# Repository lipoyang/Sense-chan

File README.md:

# ｾﾝｽﾁｬﾝ (Sense-chan)
ｾﾝｽﾁｬﾝはｽﾀｯｸﾁｬﾝ派生のSPRESENSEマイコン搭載ロボットです。  
SPRESENSE搭載のロボット用基板と対向2輪型ロボットおよびそのソフトウェアで構成されます。

## 解説

* [センスチャン ～ ｽﾀｯｸﾁｬﾝ派生のSPRESENSE搭載ロボット ～ by lipoyang | elchika](https://elchika.com/article/c5d4bbd1-0e7f-4fa6-907b-d6d020c664f9)

## ファイル
* [firmware](./firmware/) : ファームウェアのソースコード
* [mechanical](./mechanical/) : メカ部品のSTEPファイルとSTLファイル
* [board](./board/) : プリント基板の回路図とパターン設計

## SDカードにコピーするファイル

下記のファイルをマイクロSDカードにコピーして、ｾﾝｽﾁｬﾝのマイクロSDカードスロットに挿入してください。
* [fs_efont_ja_16.bin](./firmware/Sense-chan/sd_data/fs_efont_ja_16.bin) : フォントデータ
* [config.json](./firmware/Sense-chan/sd_data/config.json) : 設定ファイル

## 原典
このプロジェクトはｽﾀｯｸﾁｬﾝにインスパイアされた派生作品です。[ｽﾀｯｸﾁｬﾝ](https://github.com/stack-chan/stack-chan)は[ししかわ](https://x.com/stack_chan)さんが開発、公開している、 手乗りサイズのｽｰﾊﾟｰｶﾜｲｲコミュニケーションロボットです。

また、[B-SKY-Lab](https://x.com/eternalfriend17)さんが開発、公開している[ﾀｲﾘﾝﾁｬﾝ](https://github.com/kim-xps12/bsl-balancer)の機構設計やソフトウェアを一部参考にしています。

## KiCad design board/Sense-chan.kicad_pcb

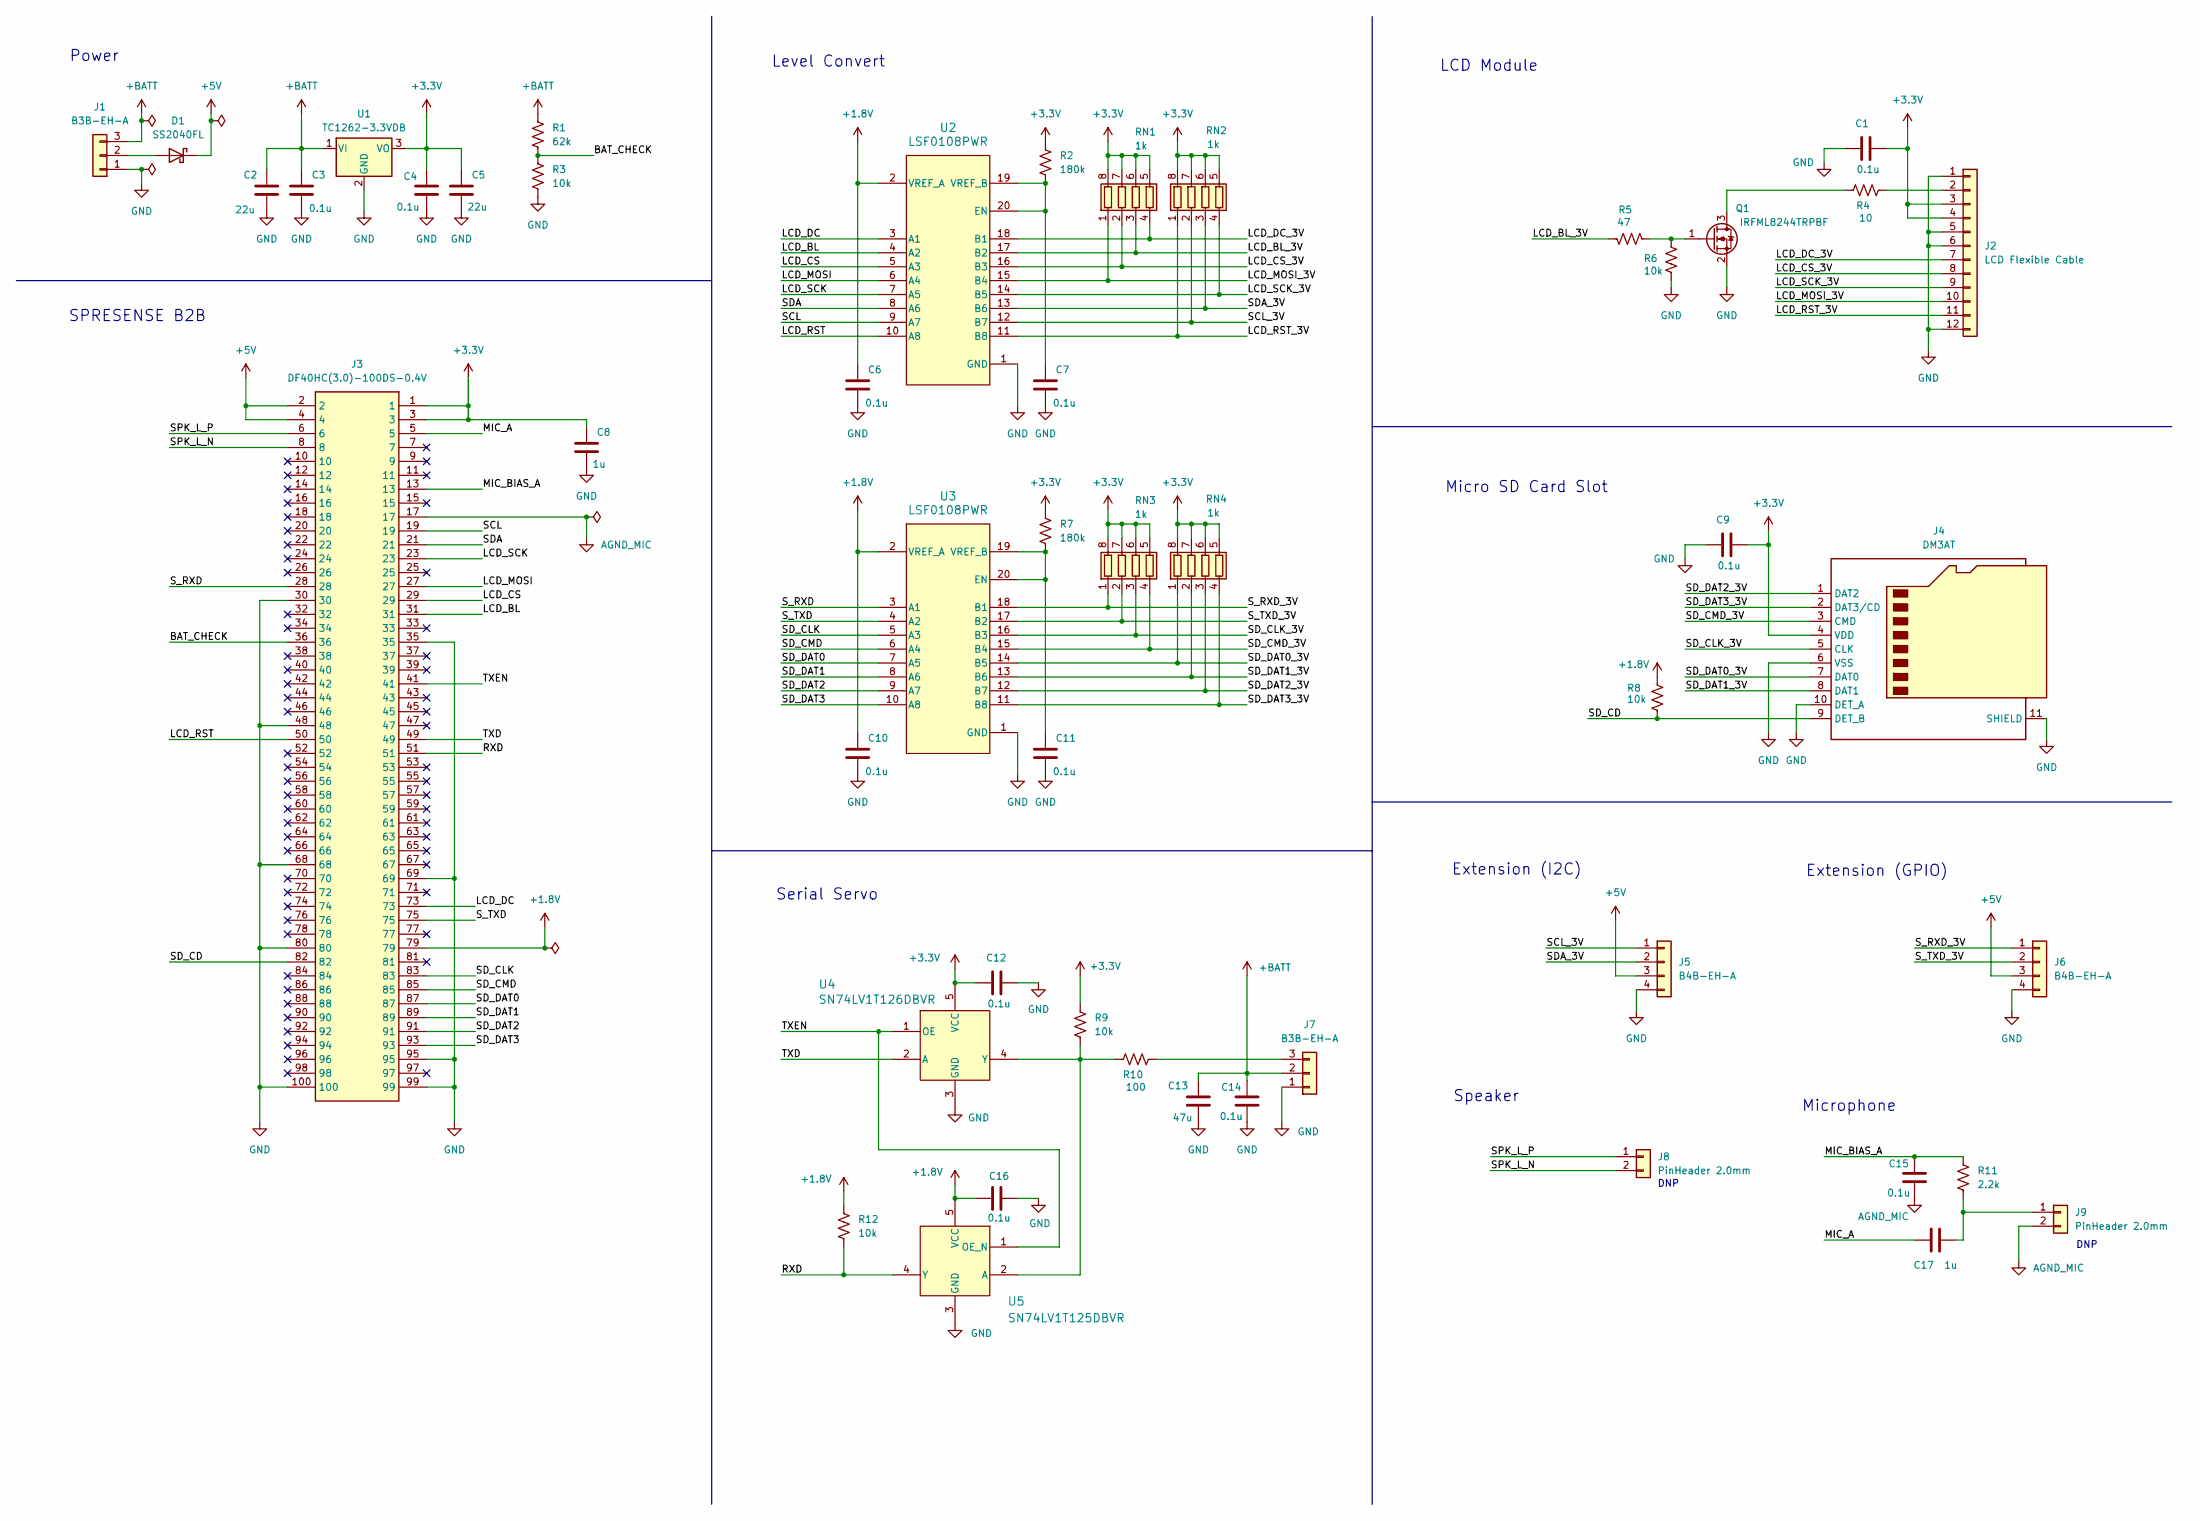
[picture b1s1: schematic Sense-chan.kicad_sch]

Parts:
C1, C3, C4, C6, C7, C9, C10, C11, C12, C14, C15, C16: 0.1u; C_0603_1608Metric; LCSC C14663
C2, C5: 22u; C_1206_3216Metric
C8: 1u; C_0603_1608Metric
C13: 47u; C_1206_3216Metric
C17: 1u; C_0603_1608Metric; LCSC C14663
D1: SS2040FL; D_SOD-123
J1, J7: B3B-EH-A; JST_EH_B3B-EH-A_1x03_P2.50mm_Vertical
J2: LCD Flexible Cable; LCD-Flex12-0.8mm
J3: DF40HC(3.0)-100DS-0.4V; spresense; Manufacturer_Part_Number DF40HC(3.0)-100DS-0.4V(51)
J4: DM3AT; microSD_HC_Hirose_DM3AT-SF-PEJM5
J5, J6: B4B-EH-A; JST_EH_B4B-EH-A_1x04_P2.50mm_Vertical
J8, J9: PinHeader 2.0mm; PinHeader_1x02_P2.00mm_Vertical
Q1: IRFML8244TRPBF; SOT-23
R1: 62k; R_0603_1608Metric
R2, R7: 180k; R_0603_1608Metric
R3, R6, R8, R9, R12: 10k; R_0603_1608Metric
R4: 10; R_0603_1608Metric
R5: 47; R_0603_1608Metric
R10: 100; R_0603_1608Metric
R11: 2.2k; R_0603_1608Metric
RN1, RN2, RN3, RN4: 1k; R_Array_Convex_4x0603
U1: TC1262-3.3VDB; SOT-223-3_TabPin2
U2, U3: LSF0108PWR; PW0020A
U4: SN74LV1T126DBVR; SOT-23-5
U5: SN74LV1T125DBVR; SOT-23-5

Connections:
+1.8V: C6.1, C10.1, C16.1, J3.79, R8.1, R12.1, U2.2 (VREF_A), U3.2 (VREF_A), U5.5 (VCC)
+3.3V: C1.2, C4.1, C5.1, C8.1, C9.2, C12.1, J2.3, J2.4, J3.1, J3.3, J4.4 (VDD), R2.1, R7.1, R9.1, RN1.5 (R4.2), RN1.6 (R3.2), RN1.7 (R2.2), RN1.8 (R1.2), RN2.5 (R4.2), RN2.6 (R3.2), RN2.7 (R2.2), RN2.8 (R1.2), RN3.5 (R4.2), RN3.6 (R3.2), RN3.7 (R2.2), RN3.8 (R1.2), RN4.5 (R4.2), RN4.6 (R3.2), RN4.7 (R2.2), RN4.8 (R1.2), U1.3 (VO), U4.5 (VCC)
+5V: D1.1 (K), J3.2, J3.4, J5.3, J6.3
+BATT: C2.1, C3.1, C13.1, C14.1, J1.3, J7.2, R1.1, U1.1 (VI)
/BAT_CHECK: J3.36, R1.2, R3.1
/LCD_BL: J3.31, U2.4 (A2)
/LCD_BL_3V: R5.1, RN1.3 (R3.1), U2.17 (B2)
/LCD_CS: J3.29, U2.5 (A3)
/LCD_CS_3V: J2.8, RN1.2 (R2.1), U2.16 (B3)
/LCD_DC: J3.73, U2.3 (A1)
/LCD_DC_3V: J2.7, RN1.4 (R4.1), U2.18 (B1)
/LCD_MOSI: J3.27, U2.6 (A4)
/LCD_MOSI_3V: J2.10, RN1.1 (R1.1), U2.15 (B4)
/LCD_RST: J3.50, U2.10 (A8)
/LCD_RST_3V: J2.11, RN2.1 (R1.1), U2.11 (B8)
/LCD_SCK: J3.23, U2.7 (A5)
/LCD_SCK_3V: J2.9, RN2.4 (R4.1), U2.14 (B5)
/MIC_A: C17.1, J3.5
/MIC_BIAS_A: C15.1, J3.13, R11.1
/RXD: J3.51, R12.2, U5.4 (Y)
/SCL: J3.19, U2.9 (A7)
/SCL_3V: J5.1, RN2.2 (R2.1), U2.12 (B7)
/SDA: J3.21, U2.8 (A6)
/SDA_3V: J5.2, RN2.3 (R3.1), U2.13 (B6)
/SD_CD: J3.82, J4.9 (DET_B), R8.2
/SD_CLK: J3.83, U3.5 (A3)
/SD_CLK_3V: J4.5 (CLK), RN3.3 (R3.1), U3.16 (B3)
/SD_CMD: J3.85, U3.6 (A4)
/SD_CMD_3V: J4.3 (CMD), RN3.4 (R4.1), U3.15 (B4)
/SD_DAT0: J3.87, U3.7 (A5)
/SD_DAT0_3V: J4.7 (DAT0), RN4.1 (R1.1), U3.14 (B5)
/SD_DAT1: J3.89, U3.8 (A6)
/SD_DAT1_3V: J4.8 (DAT1), RN4.2 (R2.1), U3.13 (B6)
/SD_DAT2: J3.91, U3.9 (A7)
/SD_DAT2_3V: J4.1 (DAT2), RN4.3 (R3.1), U3.12 (B7)
/SD_DAT3: J3.93, U3.10 (A8)
/SD_DAT3_3V: J4.2 (DAT3/CD), RN4.4 (R4.1), U3.11 (B8)
/SPK_L_N: J3.8, J8.2
/SPK_L_P: J3.6, J8.1
/S_RXD: J3.28, U3.3 (A1)
/S_RXD_3V: J6.1, RN3.1 (R1.1), U3.18 (B1)
/S_TXD: J3.75, U3.4 (A2)
/S_TXD_3V: J6.2, RN3.2 (R2.1), U3.17 (B2)
/TXD: J3.49, U4.2 (A)
/TXEN: J3.41, U4.1 (OE), U5.1 (OE_N)
AGND_MIC: C15.2, J3.17, J9.2
GND: C1.1, C2.2, C3.2, C4.2, C5.2, C6.2, C7.2, C8.2, C9.1, C10.2, C11.2, C12.2, C13.2, C14.2, C16.2, J1.1, J2.1, J2.5, J2.6, J2.12, J3.30, J3.35, J3.48, J3.68, J3.69, J3.80, J3.95, J3.99, J3.100, J4.6 (VSS), J4.10 (DET_A), J4.11 (SHIELD), J5.4, J6.4, J7.1, Q1.2 (S), R3.2, R6.2, U1.2 (GND), U2.1 (GND), U3.1 (GND), U4.3 (GND), U5.3 (GND)
unnamed: D1.2 (A), J1.2
unnamed: J2.2, R4.2
unnamed: J7.3, R10.2
unnamed: C17.2, J9.1, R11.2
unnamed: Q1.3 (D), R4.1
unnamed: Q1.1 (G), R5.2, R6.1
unnamed: C7.1, R2.2, U2.19 (VREF_B), U2.20 (EN)
unnamed: C11.1, R7.2, U3.19 (VREF_B), U3.20 (EN)
unnamed: R9.2, R10.1, U4.4 (Y), U5.2 (A)

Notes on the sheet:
Extension (I2C)
Serial Servo
Micro SD Card Slot
Speaker
SPRESENSE B2B
Extension (GPIO)
DNP
Microphone
Level Convert
Power
LCD Module

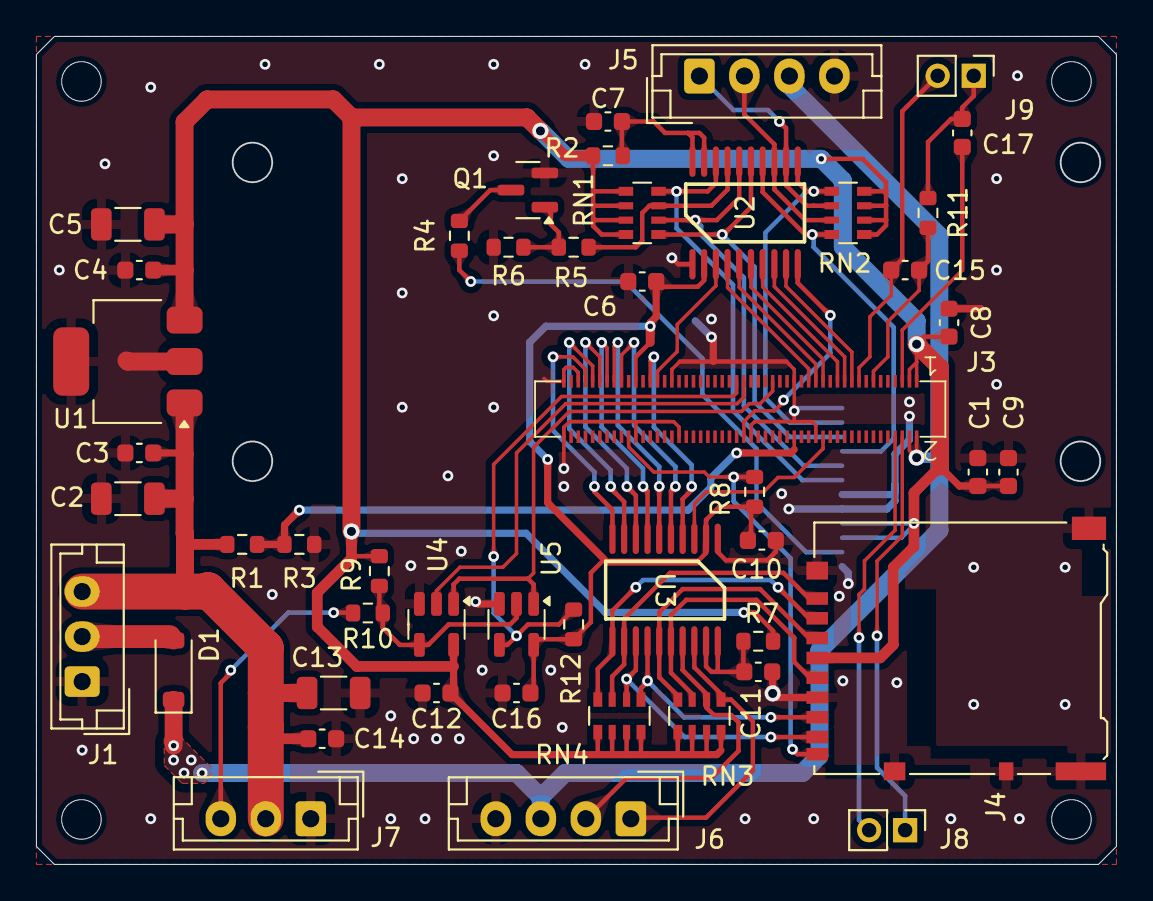
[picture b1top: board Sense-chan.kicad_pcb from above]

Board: 2 copper layers, 60.0 x 46.0 mm, 49 parts (1 on the bottom side), 56 nets.

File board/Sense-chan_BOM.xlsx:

Reference | Qty | Part Number | Description | Supplier | Supplier Code
C1, C3, C4, C6, C7, C9, C10, C11, C12, C14, C15, C16 | 12 | 0.1uF | 1608 (0603) | (在庫) | (generic)
C8, C17 | 1 | 1uF | 1608 (0603) | (在庫)ザイコ | (generic)
C2, C5 | 2 | 22uF | 3216(1206) | (在庫)ザイコ | (generic)
C13 | 1 | 47uF | 3216(1206) | (在庫)ザイコ | (generic)
R1 | 1 | 62kΩ, class F | 1608 (0603) | digikey | 10-ERJ-U03F6202VCT-ND
R3 | 1 | 10kΩ, class F | 1608 (0603) | digikey | 10-ERJ-U03F1002VCT-ND
R2, R7 | 2 | 180kΩ | 1608 (0603) | (在庫)ザイコ | (generic)
R4 | 1 | 10Ω | 1608 (0603) | (在庫)ザイコ | (generic)
R5 | 1 | 47Ω | 1608 (0603) | (在庫)ザイコ | (generic)
R6, R8, R9, R12 | 4 | 10kΩ | 1608 (0603) | (在庫)ザイコ | (generic)
R10 | 1 | 100Ω | 1608 (0603) | (在庫)ザイコ | (generic)
R11 | 1 | 2.2kΩ | 1608 (0603) | (在庫)ザイコ | (generic)
RN1, RN2, RN3, RN4 | 4 | 1kΩ×4素子 EXB-38V102JVソシ | 1608 (0603)×4素子, 凸型ソシトツガタ | digikey | Y9102CT-ND
D1 | 1 | SS2040FL | D_SOD-123 | (在庫, 秋月)ザイコアキヅキ | 102073
J1, J7 | 2 | B3B-EH-A | 日圧EH3ピン(トップ型)ニチアツガタ | (在庫, 共立)ザイコキョウリツ | 5CP14I
J2 | 1 | LCD Flexible Cable | 0.8mmピッチ 12ピン | - | -
J3 | 1 | DF40HC(3.0)-100DS-0.4V | SPRESENSE B2Bコネクタ | digikey | 26-DF40HC(3.0)-100DS-0.4V(51)CT-ND
J4 | 1 | DM3AT | ヒロセ microSDカードスロット | digikey | 26-DM3AT-SF-PEJM5(11)CT-ND
J5, J6 | 2 | B4B-EH-A | 日圧EH4ピン(トップ型)ニチアツガタ | (在庫, 共立)ザイコキョウリツ | 5CP14J
Q1 | 1 | IRFML8244TRPBF | SOT-23 | (在庫, digikey)ザイコ | IRFML8244TRPBFCT-ND
U1 | 1 | TC1262-3.3VDB | SOT-223-3_TabPin2 | (在庫, digikey)ザイコ | TC1262-3.3VDB-ND
U2, U3 | 2 | LSF0108PWR | PW0020A | digikey | 296-37828-1-ND
U4 | 1 | SN74LV1T126DBVR | SOT-23-5 | digikey | 296-37174-1-ND
U5 | 1 | SN74LV1T125DBVR | SOT-23-5 | digikey | 296-37172-1-ND

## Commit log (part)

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2025-11-24 add to README
2025-11-24 modify README
2025-12-13 add files
2025-12-13 add teardrops to PCB pattern
2025-12-13 modify PCB pattern
2025-12-13 add Gerber files
2025-12-26 modify NUS_NanoC6
2025-12-28 add mechanical data
2025-12-30 modify Sense-chan firmware
2025-12-31 modify Sense-chan firmware (LCD -> SubCore1)
2025-12-31 modify Sense-chan firmware (BLE -> SubCore2)
2025-12-31 clean up Sense-chan firmware
2025-12-31 modify Sense-chan firmware (facial expression)
2025-12-31 bug fix
2026-01-01 add screw list
2026-01-01 modify screw list
2026-01-07 modify 3D model data
2026-01-07 modify mechanical design materials
2026-01-20 add battery check
2026-01-22 modify SenseChanFace::begin()
2026-02-22 add micro motion support
2026-02-27 add SD card and JSON config data.
2026-02-28 add USB Serial command (for develop)
2026-03-26 add voice command
2026-03-28 reduce memory use
2026-03-28 reduce momory use
2026-04-03 temporarily, comment out VoiceDetector
2026-04-07 modify VoiceDetector (not use AudioClass)
2026-04-16 Avatar -> MainCore, Motor -> SubCore1
2026-04-16 add FS_U8g2font
2026-04-17 bug fix & enable VoiceDetector
